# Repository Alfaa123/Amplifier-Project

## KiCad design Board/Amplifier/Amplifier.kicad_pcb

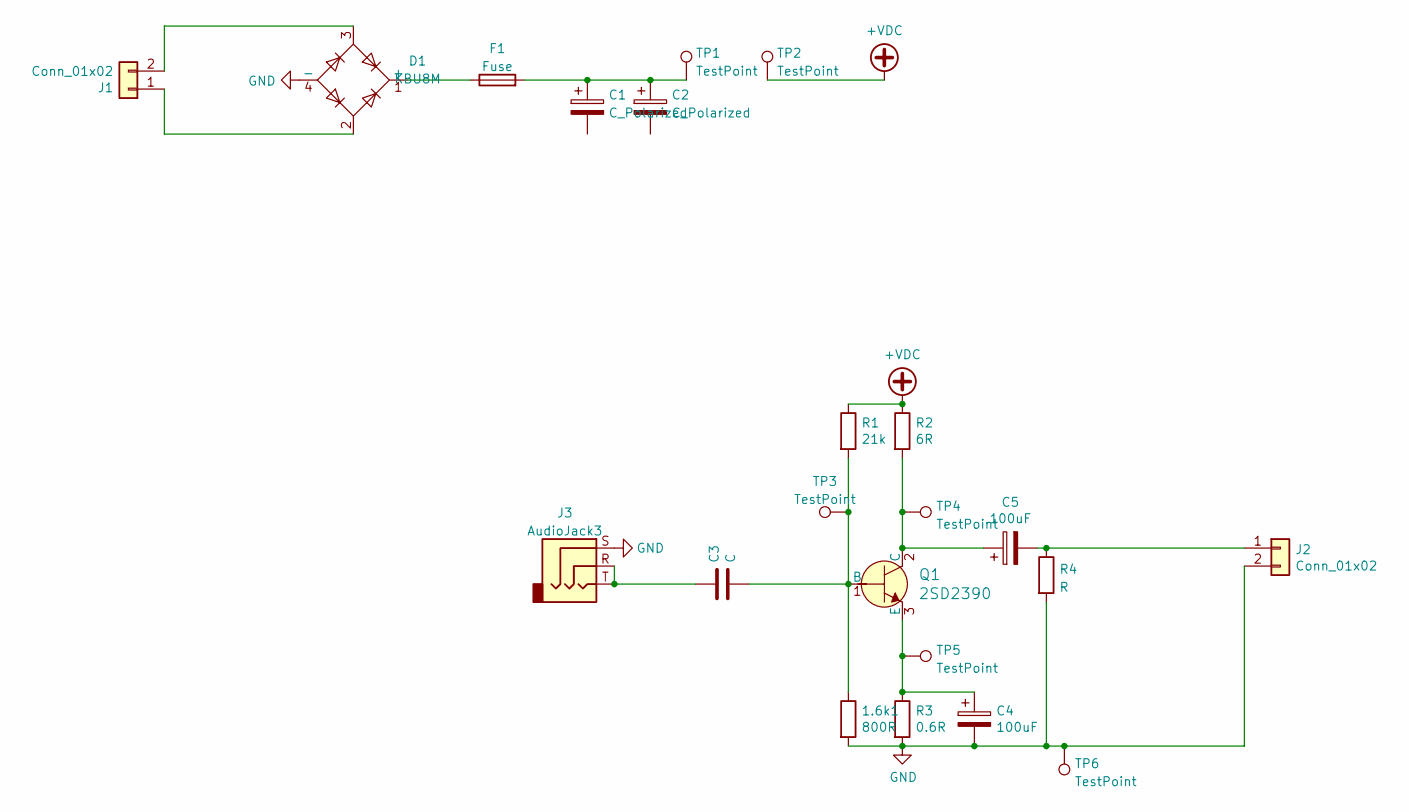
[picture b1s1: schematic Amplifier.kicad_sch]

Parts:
1.6k1: 800R; R_Axial_DIN0309_L9.0mm_D3.2mm_P12.70mm_Horizontal
C1, C2: C_Polarized; LKG1K103MKNF
C3: C; CP_Radial_D5.0mm_P2.00mm
C4, C5: 100uF; CP_Radial_D12.5mm_P5.00mm
D1: KBU8M; Diode_Bridge_Vishay_KBU
F1: Fuse; Fuseholder_Blade_Mini_Keystone_3568
J1, J2: Conn_01x02; TB005-762-02BE
J3: AudioJack3; Jack_3.5mm_CUI_SJ1-3523N_Horizontal
Q1: 2SD2390; TO-3PB-3_Horizontal_TabUp; MPN 2SD2390; Digi-Key_PN 2SD2390-ND
R1: 21k; R_Axial_DIN0309_L9.0mm_D3.2mm_P12.70mm_Horizontal
R2: 6R; TO-247-2_Horizontal_TabUp
R3: 0.6R; TO-220-2_Horizontal_TabUp
R4: R; R_Axial_DIN0309_L9.0mm_D3.2mm_P12.70mm_Horizontal
TP1, TP2, TP3, TP4, TP5, TP6: TestPoint; SolderWire-1sqmm_1x01_D1.4mm_OD3.9mm

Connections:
+VDC: R1.1, R2.1, TP2.1
GND: 1.6k1.2, C4.2, D1.4 (-), J2.2, J3.S, R3.2, R4.2, TP6.1
unnamed: 1.6k1.1, C3.2, Q1.1 (B), R1.2, TP3.1
unnamed: C1.1, C2.1, F1.2, TP1.1
unnamed: C3.1, J3.R, J3.T
unnamed: C4.1, Q1.3 (E), R3.1, TP5.1
unnamed: C5.1, Q1.2 (C), R2.2, TP4.1
unnamed: C5.2, J2.1, R4.1
unnamed: D1.1 (+), F1.1
unnamed: D1.2, J1.1
unnamed: D1.3, J1.2

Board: 2 copper layers, 22 parts (0 on the bottom side), 11 nets, no tracks yet.

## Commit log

2022-03-31 Added calculations file... Started Project
2022-04-21 Finished calculations
2022-06-07 Started picking out footprints
2022-07-06 Board design started

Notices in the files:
parts and their libraries:
Copyright 2021 Accelerated Designs. All rights reserved.
